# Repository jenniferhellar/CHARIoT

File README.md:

# CHARIoT: A Wireless, Self-Powered Sensing Node Architecture

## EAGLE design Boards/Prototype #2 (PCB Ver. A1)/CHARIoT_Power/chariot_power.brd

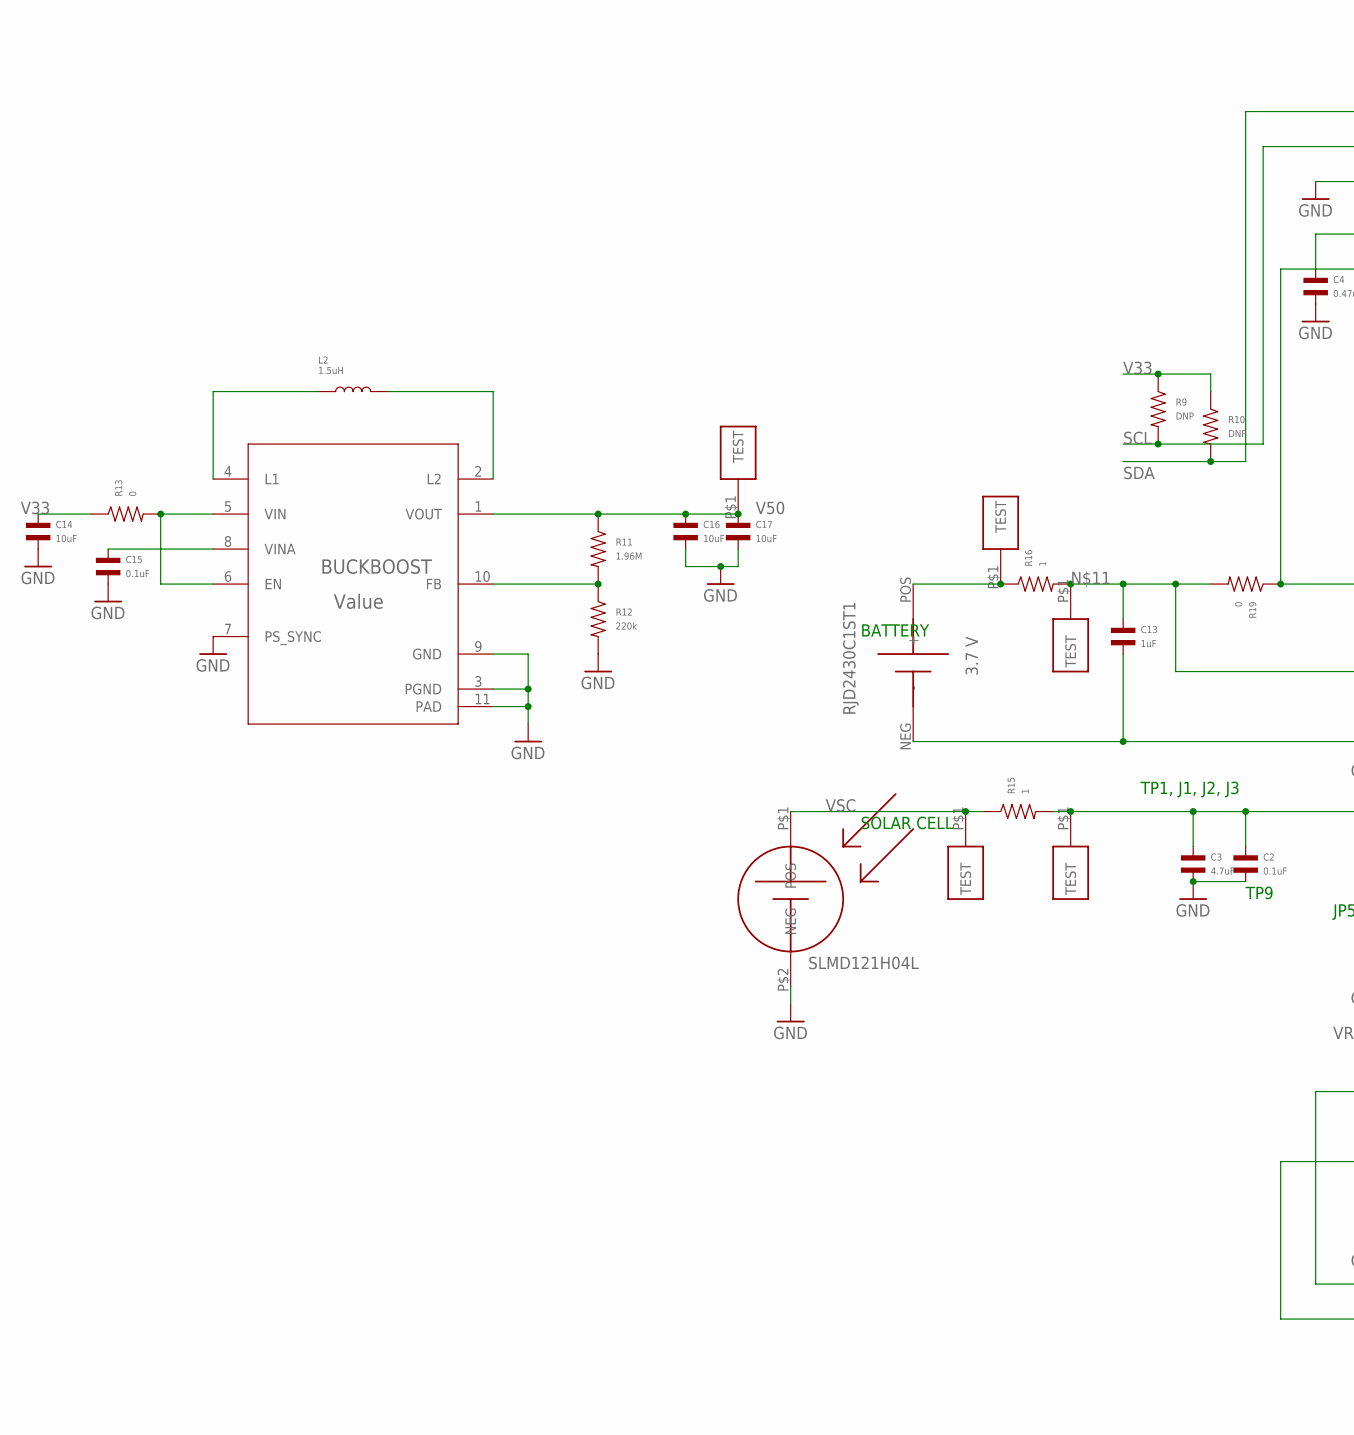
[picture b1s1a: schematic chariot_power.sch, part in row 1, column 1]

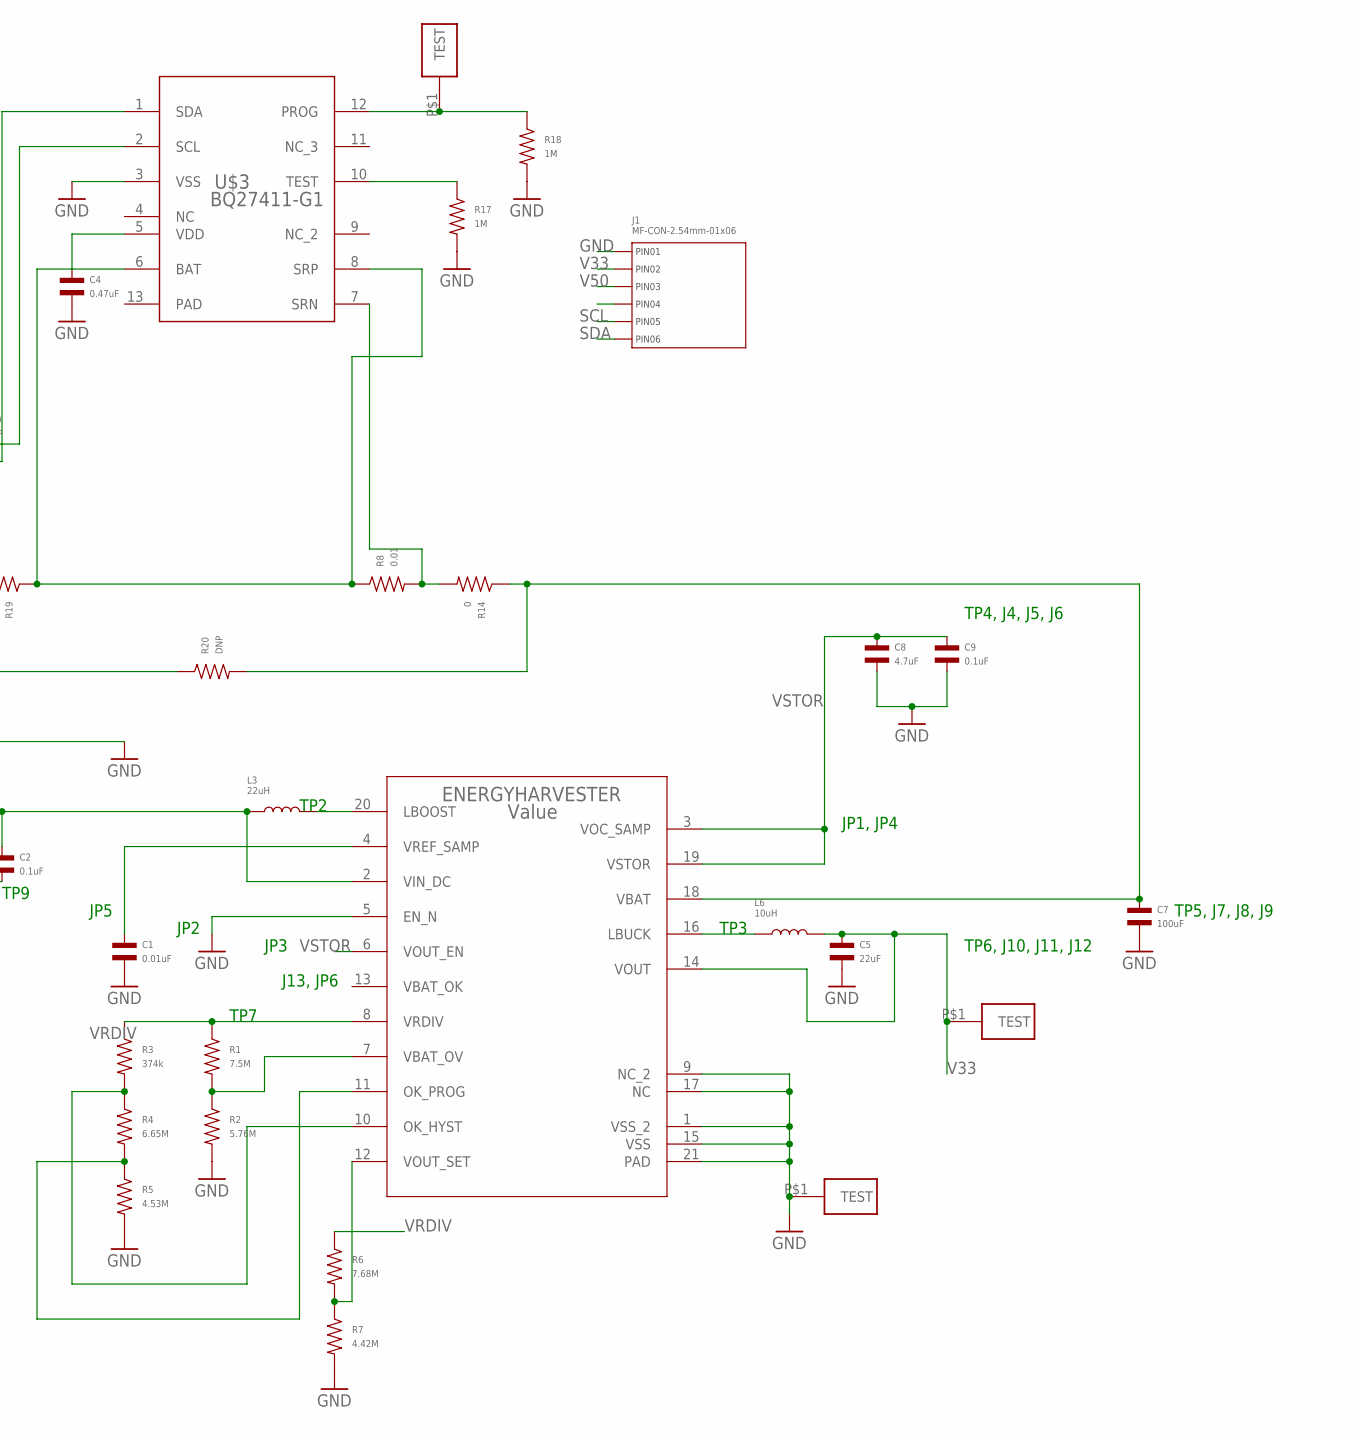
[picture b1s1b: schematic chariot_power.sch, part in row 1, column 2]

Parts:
BUCKBOOST: Value; DSK0010A
C1: 0.01uF; C0603
C2, C9, C15: 0.1uF; C0603
C3, C8: 4.7uF; C0603
C4: 0.47uF; C0603
C5: 22uF; C0603
C7: 100uF; C0603
C13: 1uF; C0603
C14, C16, C17: 10uF; C0603
ENERGYHARVESTER: Value; RGR0020A
J1: MF-CON-2.54mm-01x06; PTH_2.54MM_01X06
L2: 1.5uH; L0603
L3: 22uH; L0603
L6: 10uH; L0603
R1: 7.5M; R0603
R2: 5.76M; R0603
R3: 374k; R0603
R4: 6.65M; R0603
R5: 4.53M; R0603
R6: 7.68M; R0603
R7: 4.42M; R0603
R8: 0.01; R0603
R9, R10, R20: DNP; R0603
R11: 1.96M; R0603
R12: 220k; R0603
R13, R14, R19: 0; R0603
R15, R16: 1; R0603
R17, R18: 1M; R0603
TP1, TP2, TP3, TP4, TP5, TP6, TP7, TP8: TESTPOINT_LOOP
U$1: SLMD121H04L
U$2: RJD2430C1ST1.; RJD2430C1ST1
U$3: BQ27411-G1; DRZ0012A

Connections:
EXT_VCC: J1.P$4 (PIN4)
GND: BUCKBOOST.3 (PGND), BUCKBOOST.7 (PS_SYNC), BUCKBOOST.9 (GND), BUCKBOOST.11 (PAD), C1.P$2, C2.P$2, C3.P$2, C4.P$2, C5.P$2, C7.P$2, C8.P$2, C9.P$2, C13.P$2, C14.P$2, C15.P$2, C16.P$2, C17.P$2, ENERGYHARVESTER.1 (VSS_2), ENERGYHARVESTER.5 (EN_N), ENERGYHARVESTER.9 (NC_2), ENERGYHARVESTER.15 (VSS), ENERGYHARVESTER.17 (NC), ENERGYHARVESTER.21 (PAD), J1.P$1 (PIN1), R2.P$2, R5.P$2, R7.P$2, R12.P$2, R17.P$2, R18.P$2, TP1.P$1, U$1.P$2 (NEG), U$2.NEG (-), U$3.3 (VSS)
unnamed: C1.P$1, ENERGYHARVESTER.4 (VREF_SAMP)
unnamed: ENERGYHARVESTER.20 (LBOOST), L3.P$2
unnamed: C7.P$1, ENERGYHARVESTER.18 (VBAT), R14.P$1, R20.P$2
unnamed: ENERGYHARVESTER.16 (LBUCK), L6.P$1
unnamed: C14.P$1, R13.P$1
unnamed: ENERGYHARVESTER.7 (VBAT_OV), R1.P$2, R2.P$1
unnamed: ENERGYHARVESTER.12 (VOUT_SET), R6.P$2, R7.P$1
unnamed: R17.P$1, U$3.10 (TEST)
unnamed: ENERGYHARVESTER.10 (OK_HYST), R3.P$2, R4.P$1
unnamed: ENERGYHARVESTER.11 (OK_PROG), R4.P$2, R5.P$1
unnamed: C13.P$1, R16.P$2, R19.P$2, R20.P$1, TP7.P$1
unnamed: BUCKBOOST.4 (L1), L2.P$1
unnamed: R8.P$2, R14.P$2, U$3.7 (SRN)
unnamed: R18.P$1, TP8.P$1, U$3.12 (PROG)
unnamed: C4.P$1, U$3.5 (VDD)
unnamed: BUCKBOOST.2 (L2), L2.P$2
unnamed: BUCKBOOST.8 (VINA), C15.P$1
unnamed: BUCKBOOST.10 (FB), R11.P$2, R12.P$1
SCL: J1.P$5 (PIN5), R9.P$2, U$3.2 (SCL)
SDA: J1.P$6 (PIN6), R10.P$2, U$3.1 (SDA)
V33: BUCKBOOST.5 (VIN), BUCKBOOST.6 (EN), C5.P$1, ENERGYHARVESTER.14 (VOUT), J1.P$2 (PIN2), L6.P$2, R9.P$1, R10.P$1, R13.P$2, TP2.P$1
V50: BUCKBOOST.1 (VOUT), C16.P$1, C17.P$1, J1.P$3 (PIN3), R11.P$1, TP3.P$1
VBAT: R16.P$1, TP5.P$1, U$2.POS (+)
VBAT2: R8.P$1, R19.P$1, U$3.6 (BAT), U$3.8 (SRP)
VIN1: C2.P$1, C3.P$1, ENERGYHARVESTER.2 (VIN_DC), L3.P$1, R15.P$2, TP6.P$1
VRDIV: ENERGYHARVESTER.8 (VRDIV), R1.P$1, R3.P$1, R6.P$1
VSC: R15.P$1, TP4.P$1, U$1.P$1 (POS)
VSTOR: C8.P$1, C9.P$1, ENERGYHARVESTER.3 (VOC_SAMP), ENERGYHARVESTER.6 (VOUT_EN), ENERGYHARVESTER.19 (VSTOR)

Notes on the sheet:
TP2
JP5
JP2
TP9
TP3
TP6, J10, J11, J12
TP1, J1, J2, J3
J13, JP6
TP5, J7, J8, J9
JP3
TP7
JP1, JP4
TP4, J4, J5, J6
SOLAR CELL
BATTERY

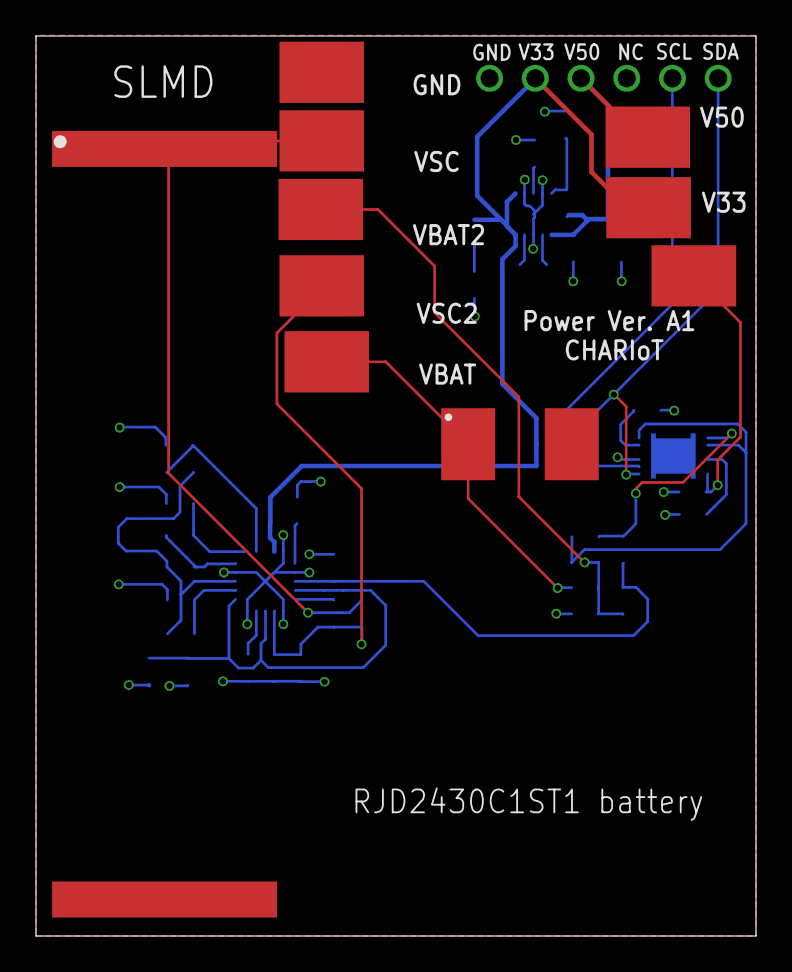
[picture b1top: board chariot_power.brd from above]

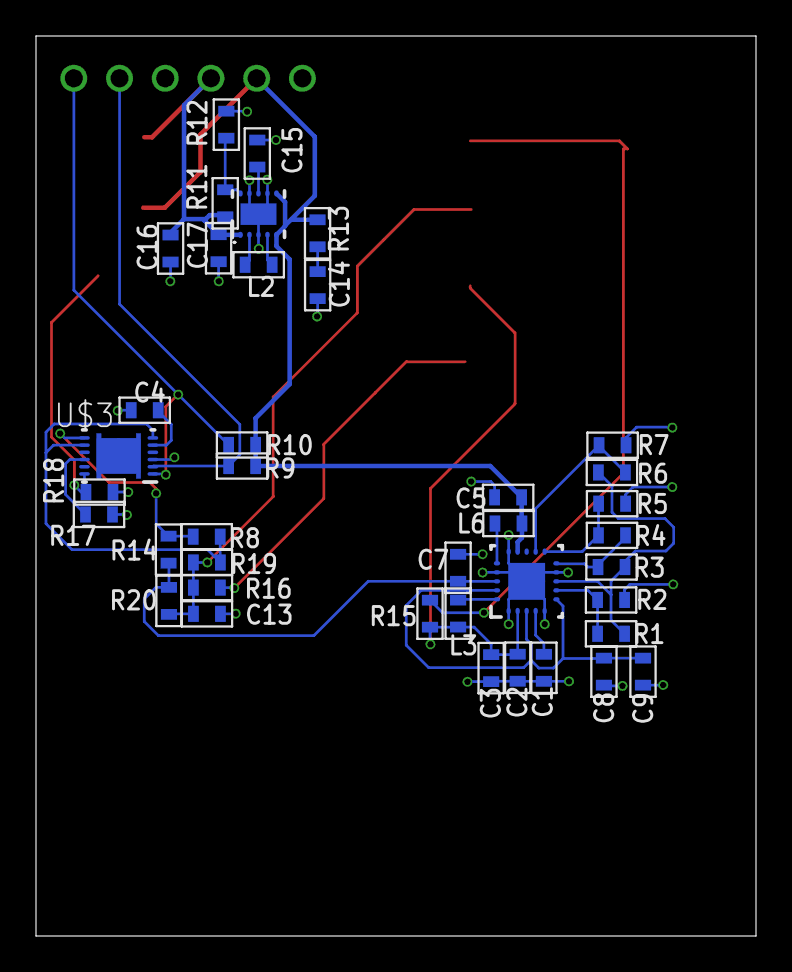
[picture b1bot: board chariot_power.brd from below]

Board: 2 copper layers, 40.0 x 50.0 mm, 50 parts (39 on the bottom side), 29 nets.

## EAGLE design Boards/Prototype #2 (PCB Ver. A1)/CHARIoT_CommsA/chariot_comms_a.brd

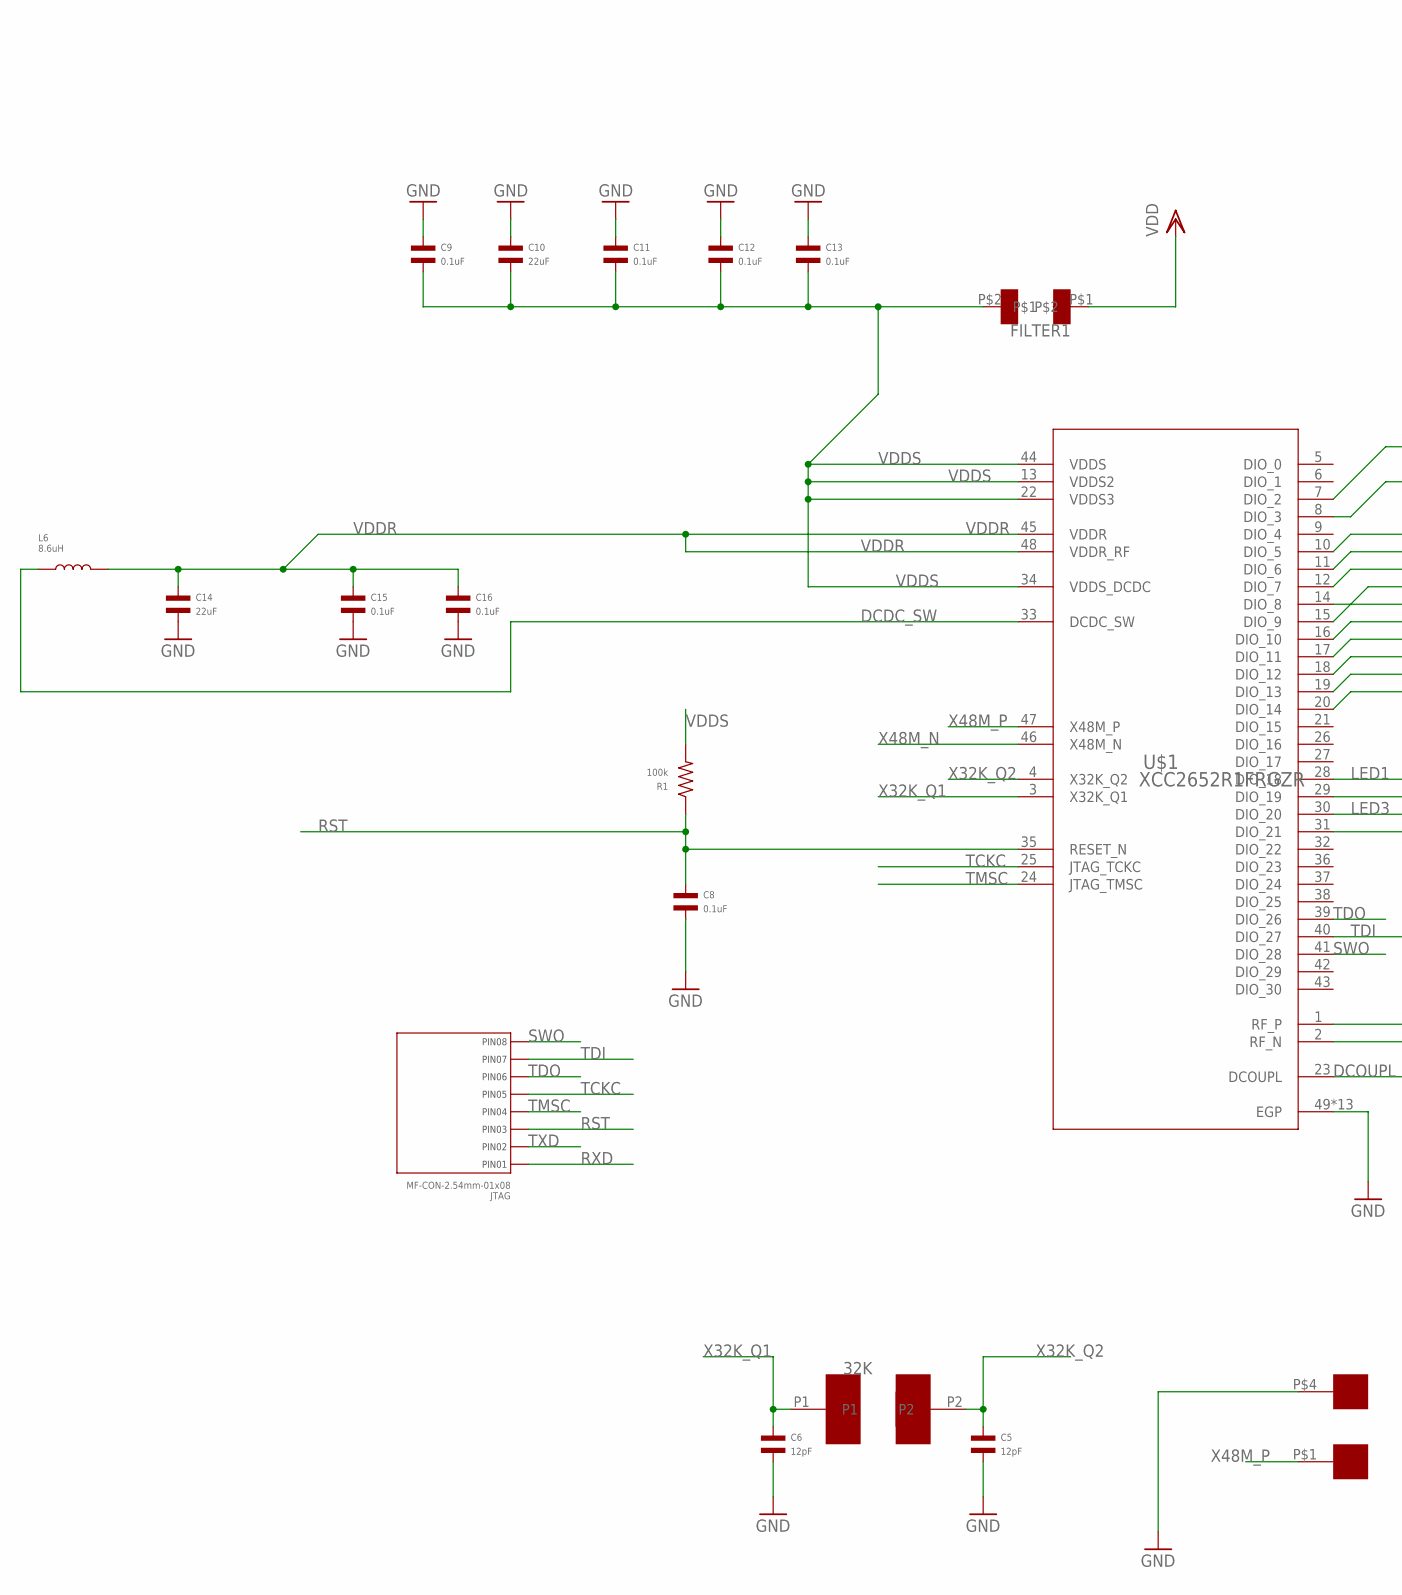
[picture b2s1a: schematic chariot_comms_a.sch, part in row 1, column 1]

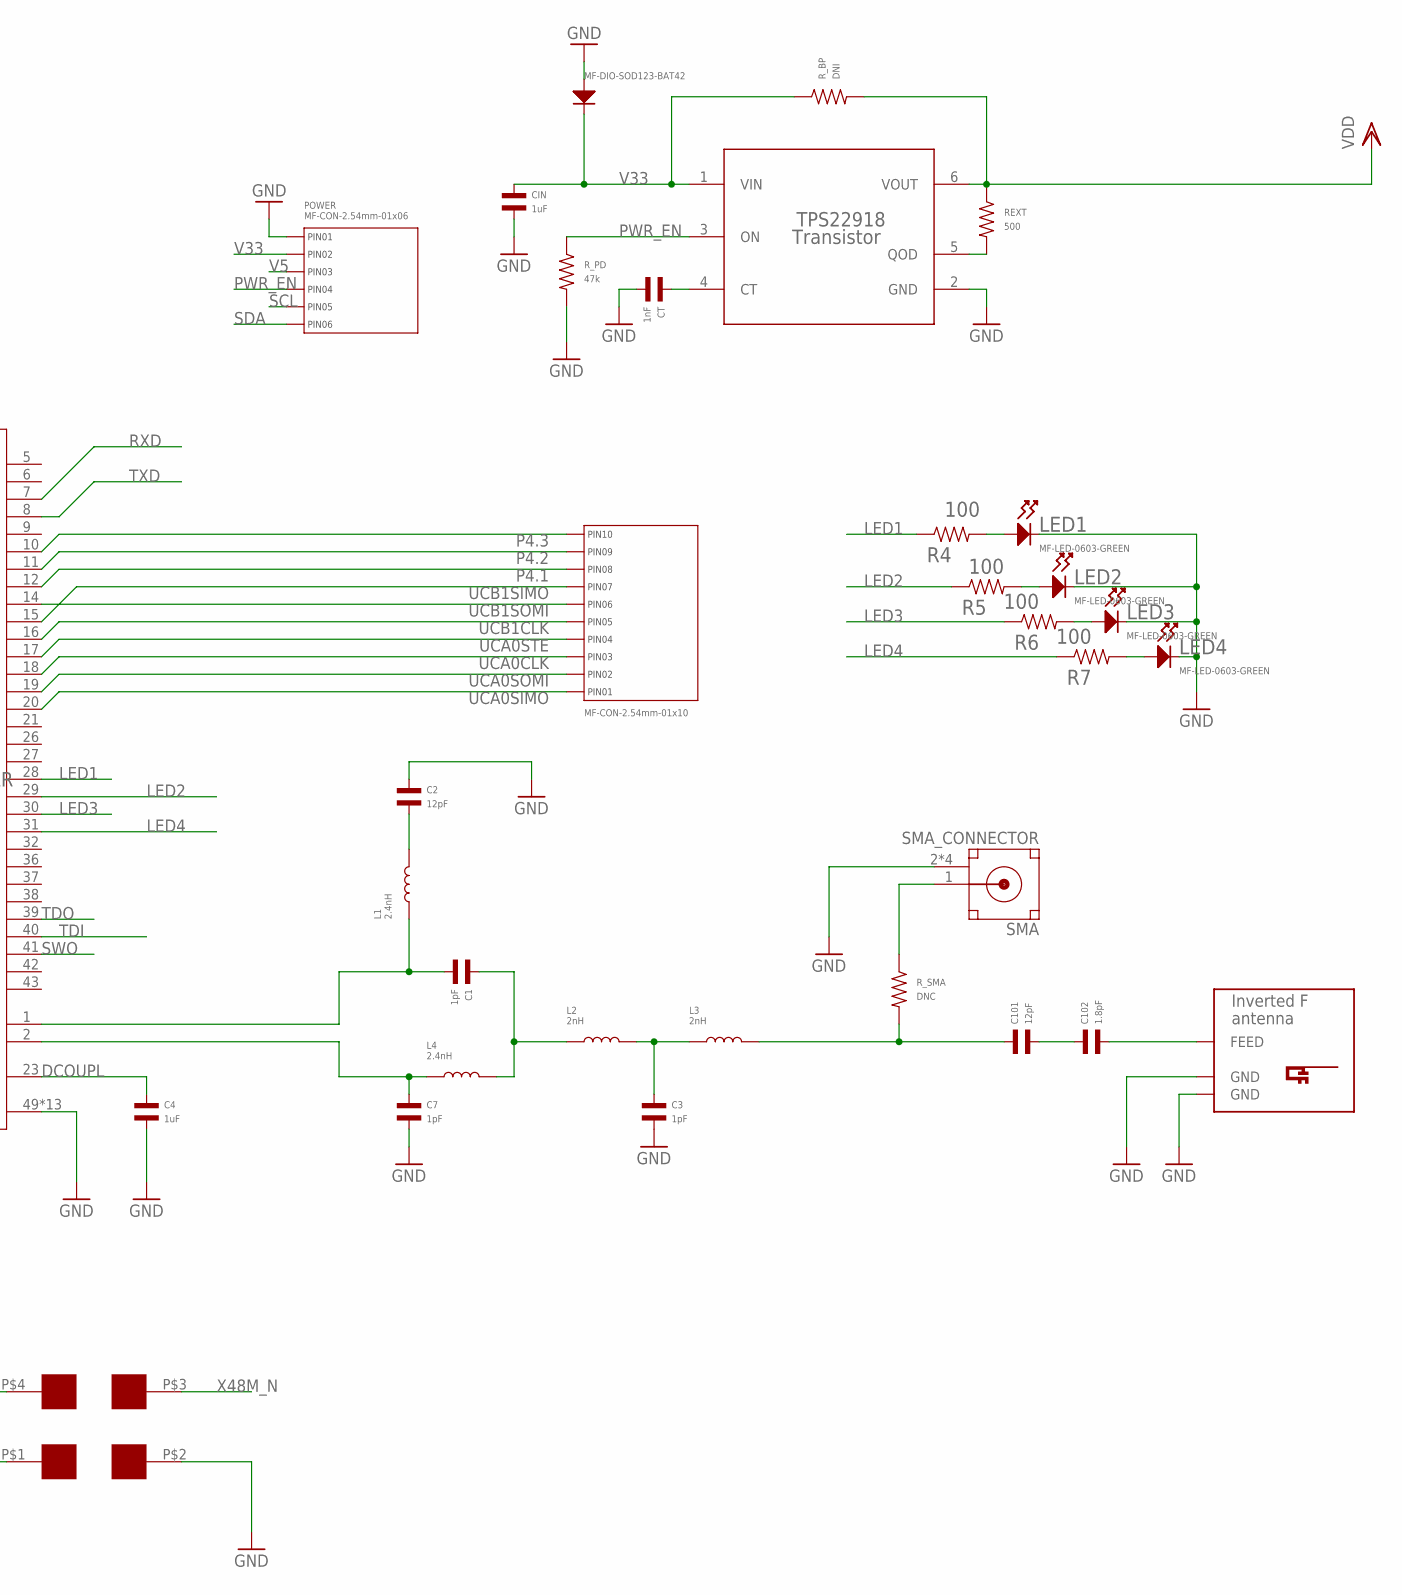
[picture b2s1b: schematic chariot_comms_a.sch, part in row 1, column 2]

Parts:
32K: FC-135
48M: NX2016SA-48M-EXS00A-CS05517
C1, C3, C7: 1pF; C0603
C2, C5, C6, C101: 12pF; C0603
C4: 1uF; C0603
C8, C9, C11, C12, C13, C15, C16: 0.1uF; C0603
C10, C14: 22uF; C0603
C102: 1.8pF; C0603
CIN: 1uF; C0603
COMMS_J: MF-CON-2.54mm-01x10; PTH_2.54MM_01X10
CT: 1nF; C0603
D1: MF-DIO-SOD123-BAT42; SOD-123
FILTER1: BLM18HE152SN1D
JTAG: MF-CON-2.54mm-01x08; PTH_2.54MM_01X08
L1, L4: 2.4nH; L0603
L2, L3: 2nH; L0603
L6: 8.6uH; L0603
LED1, LED2, LED3, LED4: MF-LED-0603-GREEN; LED0603
POWER: MF-CON-2.54mm-01x06; PTH_2.54MM_01X06
R1: 100k; R0603
R4, R5, R6, R7: 100; R0603
REXT: 500; R0603
R_BP: DNI; R0603
R_PD: 47k; R0603
R_SMA: DNC; R0603
SMA: SMA_CONNECTOR; LPRS_SMA_CONNECTOR
TPS22918: Transistor; DBV0006A_N
U$1: XCC2652R1FRGZR; RGZ0048A
U$2: INVERTED_F_ANTENNA+5; DN007+5

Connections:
DCDC_SW: L6.P$1, U$1.33 (DCDC_SW)
DCOUPL: C4.P$1, U$1.23 (DCOUPL)
GND: 48M.P$2, 48M.P$4, C2.P$1, C3.P$2, C4.P$2, C5.P$2, C6.P$2, C7.P$2, C8.P$2, C9.P$1, C10.P$1, C11.P$1, C12.P$1, C13.P$1, C14.P$2, C15.P$2, C16.P$2, CIN.P$2, CT.P$2, D1.ANODE, LED1.CATHODE, LED2.CATHODE, LED3.CATHODE, LED4.CATHODE, POWER.P$1 (PIN1), R_PD.P$2, SMA.2 (GND), SMA.3 (GND), SMA.4 (GND), SMA.5 (GND), TPS22918.2 (GND), U$1.49 (EGP), U$1.V1 (EGP), U$1.V2 (EGP), U$1.V3 (EGP), U$1.V4 (EGP), U$1.V5 (EGP), U$1.V6 (EGP), U$1.V7 (EGP), U$1.V8 (EGP), U$1.V9 (EGP), U$1.V10 (EGP), U$1.V11 (EGP), U$1.V12 (EGP), U$2.GND, U$2.GND@1 (GND)
LED1: R4.P$1, U$1.28 (DIO_18)
LED2: R5.P$1, U$1.29 (DIO_19)
LED3: R6.P$1, U$1.30 (DIO_20)
LED4: R7.P$1, U$1.31 (DIO_21)
unnamed: C102.P$2, U$2.FEED
unnamed: LED1.ANODE, R4.P$2
unnamed: C2.P$2, L1.P$2
unnamed: C1.P$1, L2.P$1, L4.P$2
unnamed: C3.P$1, L2.P$2, L3.P$1
unnamed: C101.P$1, L3.P$2, R_SMA.P$2
unnamed: C101.P$2, C102.P$1
unnamed: LED2.ANODE, R5.P$2
unnamed: REXT.P$2, TPS22918.5 (QOD)
unnamed: CT.P$1, TPS22918.4 (CT)
unnamed: LED3.ANODE, R6.P$2
unnamed: LED4.ANODE, R7.P$2
unnamed: R_SMA.P$1, SMA.1 (SIG)
P4.1: COMMS_J.P$8 (PIN8), U$1.12 (DIO_7)
P4.2: COMMS_J.P$9 (PIN9), U$1.11 (DIO_6)
P4.3: COMMS_J.P$10 (PIN10), U$1.10 (DIO_5)
PWR_EN: POWER.P$4 (PIN4), R_PD.P$1, TPS22918.3 (ON)
RF_N: C7.P$1, L4.P$1, U$1.2 (RF_N)
RF_P: C1.P$2, L1.P$1, U$1.1 (RF_P)
RST: C8.P$1, JTAG.P$3 (PIN3), R1.P$1, U$1.35 (RESET_N)
RXD: JTAG.P$1 (PIN1), U$1.7 (DIO_2)
SCL: POWER.P$5 (PIN5)
SDA: POWER.P$6 (PIN6)
SWO: JTAG.P$8 (PIN8), U$1.41 (DIO_28)
TCKC: JTAG.P$5 (PIN5), U$1.25 (JTAG_TCKC)
TDI: JTAG.P$7 (PIN7), U$1.40 (DIO_27)
TDO: JTAG.P$6 (PIN6), U$1.39 (DIO_26)
TMSC: JTAG.P$4 (PIN4), U$1.24 (JTAG_TMSC)
TXD: JTAG.P$2 (PIN2), U$1.8 (DIO_3)
UCA0CLK: COMMS_J.P$3 (PIN3), U$1.18 (DIO_12)
UCA0SIMO: COMMS_J.P$1 (PIN1), U$1.20 (DIO_14)
UCA0SOMI: COMMS_J.P$2 (PIN2), U$1.19 (DIO_13)
UCA0STE: COMMS_J.P$4 (PIN4), U$1.17 (DIO_11)
UCB1CLK: COMMS_J.P$5 (PIN5), U$1.16 (DIO_10)
UCB1SIMO: COMMS_J.P$7 (PIN7), U$1.15 (DIO_9)
UCB1SOMI: COMMS_J.P$6 (PIN6), U$1.14 (DIO_8)
V5: POWER.P$3 (PIN3)
V33: CIN.P$1, D1.CATHODE, POWER.P$2 (PIN2), R_BP.P$1, TPS22918.1 (VIN)
VDD: FILTER1.P$1, REXT.P$1, R_BP.P$2, TPS22918.6 (VOUT)
VDDR: C14.P$1, C15.P$1, C16.P$1, L6.P$2, U$1.45 (VDDR), U$1.48 (VDDR_RF)
VDDS: C9.P$2, C10.P$2, C11.P$2, C12.P$2, C13.P$2, FILTER1.P$2, R1.P$2, U$1.13 (VDDS2), U$1.22 (VDDS3), U$1.34 (VDDS_DCDC), U$1.44 (VDDS)
X32K_Q1: 32K.P1, C6.P$1, U$1.3 (X32K_Q1)
X32K_Q2: 32K.P2, C5.P$1, U$1.4 (X32K_Q2)
X48M_N: 48M.P$3, U$1.46 (X48M_N)
X48M_P: 48M.P$1, U$1.47 (X48M_P)

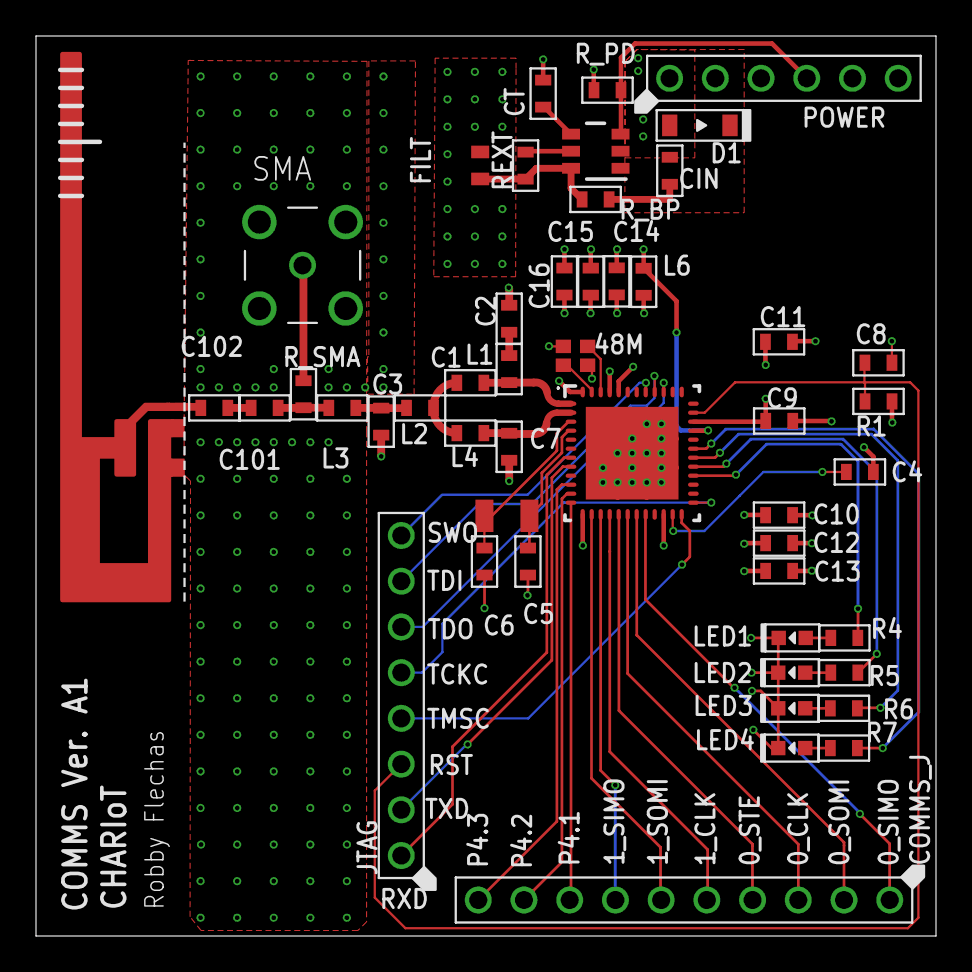
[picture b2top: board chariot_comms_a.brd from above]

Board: 4 copper layers, 50.0 x 50.0 mm, 49 parts (0 on the bottom side), 49 nets.

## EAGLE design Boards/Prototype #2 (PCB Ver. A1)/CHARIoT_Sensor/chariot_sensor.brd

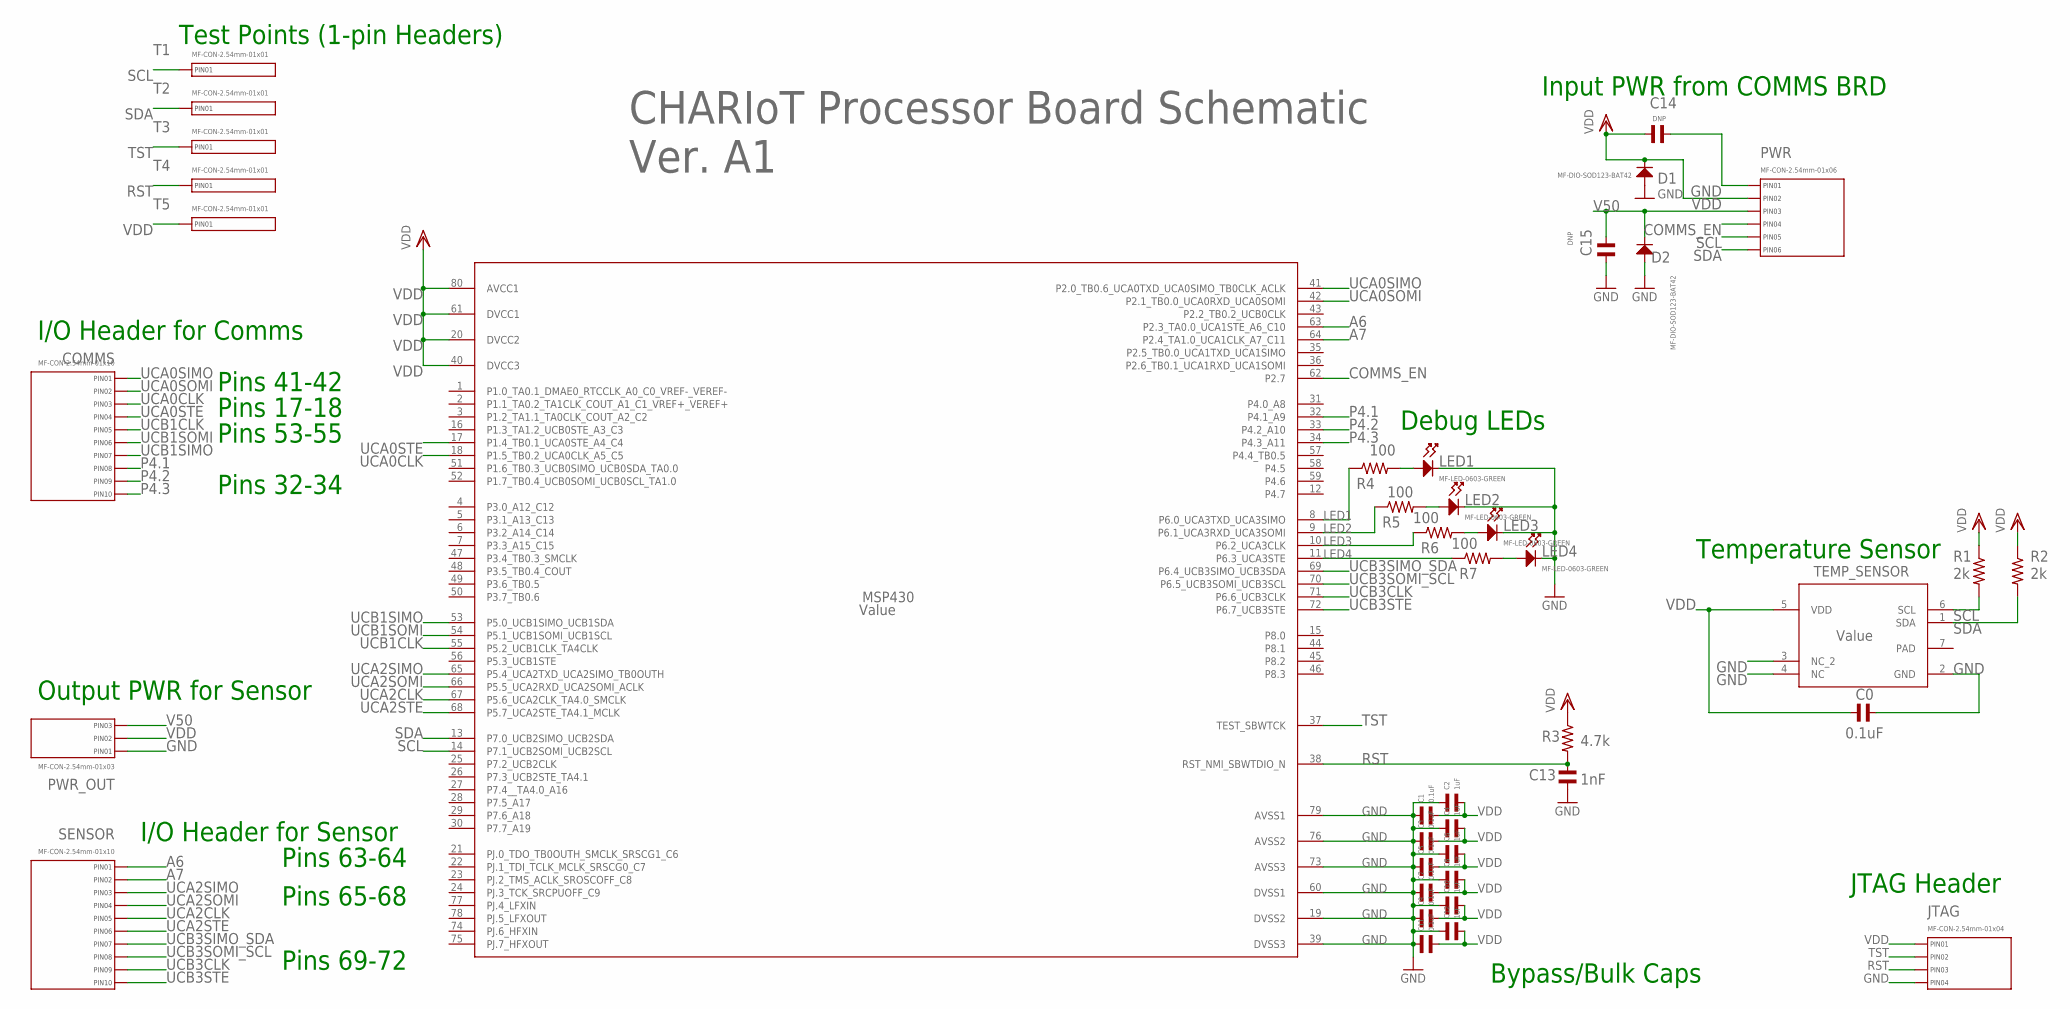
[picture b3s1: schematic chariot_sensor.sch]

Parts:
C0, C1, C3, C5, C7, C9, C11: 0.1uF; C0603
C2, C4, C6, C8, C10, C12: 1uF; C0603
C13: 1nF; C0603
C14, C15: DNP; C0603
COMMS: MF-CON-2.54mm-01x10; PTH_2.54MM_01X10
D1, D2: MF-DIO-SOD123-BAT42; SOD-123
JTAG: MF-CON-2.54mm-01x04; PTH_2.54MM_01X04
LED1, LED2, LED3, LED4: MF-LED-0603-GREEN; LED0603
MSP430: Value; PN0080A_N
PWR: MF-CON-2.54mm-01x06; PTH_2.54MM_01X06
PWR_OUT: MF-CON-2.54mm-01x03; PTH_2.54MM_01X03
R1, R2: 2k; R0603
R3: 4.7k; R0603
R4, R5, R6, R7: 100; R0603
SENSOR: MF-CON-2.54mm-01x10; PTH_2.54MM_01X10
T1, T2, T3, T4, T5: MF-CON-2.54mm-01x01; PTH_2.54MM_01X01
TEMP_SENSOR: Value; DMB0006A

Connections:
A6: MSP430.63 (P2.3_TA0.0_UCA1STE_A6_C10), SENSOR.P$1 (PIN1)
A7: MSP430.64 (P2.4_TA1.0_UCA1CLK_A7_C11), SENSOR.P$2 (PIN2)
COMMS_EN: MSP430.62 (P2.7), PWR.P$4 (PIN4)
GND: C0.P$2, C1.P$1, C2.P$1, C3.P$1, C4.P$1, C5.P$1, C6.P$1, C7.P$1, C8.P$1, C9.P$1, C10.P$1, C11.P$1, C12.P$1, C13.P$2, C14.P$2, C15.P$2, D1.ANODE, D2.ANODE, JTAG.P$4 (PIN4), LED1.CATHODE, LED2.CATHODE, LED3.CATHODE, LED4.CATHODE, MSP430.19 (DVSS2), MSP430.39 (DVSS3), MSP430.60 (DVSS1), MSP430.73 (AVSS3), MSP430.76 (AVSS2), MSP430.79 (AVSS1), PWR.P$1 (PIN1), PWR_OUT.P$1 (PIN1), TEMP_SENSOR.2 (GND), TEMP_SENSOR.3 (NC_2), TEMP_SENSOR.4 (NC)
LED1: MSP430.8 (P6.0_UCA3TXD_UCA3SIMO), R4.P$1
LED2: MSP430.9 (P6.1_UCA3RXD_UCA3SOMI), R5.P$1
LED3: MSP430.10 (P6.2_UCA3CLK), R6.P$1
LED4: MSP430.11 (P6.3_UCA3STE), R7.P$1
unnamed: LED1.ANODE, R4.P$2
unnamed: LED2.ANODE, R5.P$2
unnamed: LED3.ANODE, R6.P$2
unnamed: LED4.ANODE, R7.P$2
P4.1: COMMS.P$8 (PIN8), MSP430.32 (P4.1_A9)
P4.2: COMMS.P$9 (PIN9), MSP430.33 (P4.2_A10)
P4.3: COMMS.P$10 (PIN10), MSP430.34 (P4.3_A11)
PAD: TEMP_SENSOR.7 (PAD)
RST: C13.P$1, JTAG.P$3 (PIN3), MSP430.38 (RST_NMI_SBWTDIO_N), R3.P$2, T4.P$1
SCL: MSP430.14 (P7.1_UCB2SOMI_UCB2SCL), PWR.P$5 (PIN5), R1.P$2, T1.P$1, TEMP_SENSOR.6 (SCL)
SDA: MSP430.13 (P7.0_UCB2SIMO_UCB2SDA), PWR.P$6 (PIN6), R2.P$2, T2.P$1, TEMP_SENSOR.1 (SDA)
TST: JTAG.P$2 (PIN2), MSP430.37 (TEST_SBWTCK), T3.P$1
UCA0CLK: COMMS.P$3 (PIN3), MSP430.18 (P1.5_TB0.2_UCA0CLK_A5_C5)
UCA0SIMO: COMMS.P$1 (PIN1), MSP430.41 (P2.0_TB0.6_UCA0TXD_UCA0SIMO_TB0CLK_ACLK)
UCA0SOMI: COMMS.P$2 (PIN2), MSP430.42 (P2.1_TB0.0_UCA0RXD_UCA0SOMI)
UCA0STE: COMMS.P$4 (PIN4), MSP430.17 (P1.4_TB0.1_UCA0STE_A4_C4)
UCA2CLK: MSP430.67 (P5.6_UCA2CLK_TA4.0_SMCLK), SENSOR.P$5 (PIN5)
UCA2SIMO: MSP430.65 (P5.4_UCA2TXD_UCA2SIMO_TB0OUTH), SENSOR.P$3 (PIN3)
UCA2SOMI: MSP430.66 (P5.5_UCA2RXD_UCA2SOMI_ACLK), SENSOR.P$4 (PIN4)
UCA2STE: MSP430.68 (P5.7_UCA2STE_TA4.1_MCLK), SENSOR.P$6 (PIN6)
UCB1CLK: COMMS.P$5 (PIN5), MSP430.55 (P5.2_UCB1CLK_TA4CLK)
UCB1SIMO: COMMS.P$7 (PIN7), MSP430.53 (P5.0_UCB1SIMO_UCB1SDA)
UCB1SOMI: COMMS.P$6 (PIN6), MSP430.54 (P5.1_UCB1SOMI_UCB1SCL)
UCB3CLK: MSP430.71 (P6.6_UCB3CLK), SENSOR.P$9 (PIN9)
UCB3SIMO_SDA: MSP430.69 (P6.4_UCB3SIMO_UCB3SDA), SENSOR.P$7 (PIN7)
UCB3SOMI_SCL: MSP430.70 (P6.5_UCB3SOMI_UCB3SCL), SENSOR.P$8 (PIN8)
UCB3STE: MSP430.72 (P6.7_UCB3STE), SENSOR.P$10 (PIN10)
V50: C15.P$1, D2.CATHODE, PWR.P$3 (PIN3), PWR_OUT.P$3 (PIN3)
VDD: C0.P$1, C1.P$2, C2.P$2, C3.P$2, C4.P$2, C5.P$2, C6.P$2, C7.P$2, C8.P$2, C9.P$2, C10.P$2, C11.P$2, C12.P$2, C14.P$1, D1.CATHODE, JTAG.P$1 (PIN1), MSP430.20 (DVCC2), MSP430.40 (DVCC3), MSP430.61 (DVCC1), MSP430.80 (AVCC1), PWR.P$2 (PIN2), PWR_OUT.P$2 (PIN2), R1.P$1, R2.P$1, R3.P$1, T5.P$1, TEMP_SENSOR.5 (VDD)

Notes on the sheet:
Test Points (1-pin Headers)
Pins 17-18
Pins 53-55
Pins 41-42
Pins 32-34
Input PWR from COMMS BRD
Temperature Sensor
JTAG Header
Debug LEDs
Output PWR for Sensor
I/O Header for Sensor
Bypass/Bulk Caps
I/O Header for Comms
Pins 63-64
Pins 65-68
Pins 69-72
CHARIoT Processor Board Schematic Ver. A1

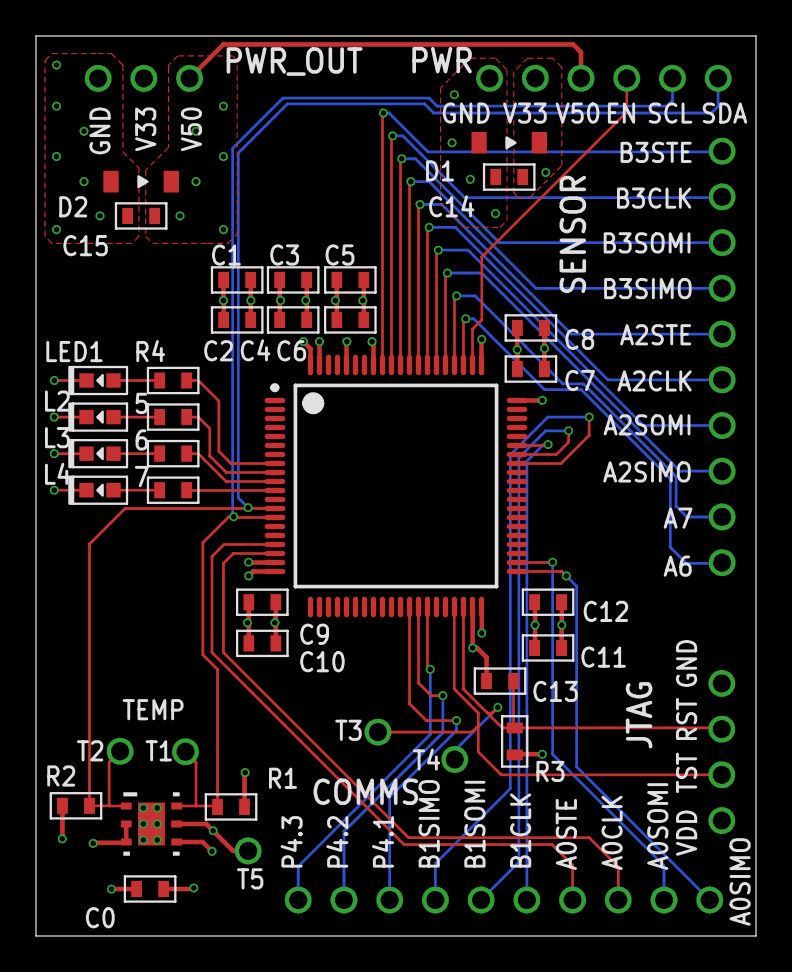
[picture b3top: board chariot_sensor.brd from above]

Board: 4 copper layers, 40.0 x 50.0 mm, 41 parts (0 on the bottom side), 36 nets.
